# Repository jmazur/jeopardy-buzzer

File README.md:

# Jeopardy Buzzer
This project is a Jeopardy! inspired buzzer for home use. You can connect up to
10 contestants and 1 host to play trivia game. The first contestant to buzz in
locks all the other contestants out. 

The buzzers communicate over a local WIFI which can be configured in the
firmware.

## Hardware
This project uses an ESP 32 S2 SOLO. All schematics and PCB design was completed
using KiCAD. The full project can be found in the `pcb` folder.

There is a known issue with the spacing of the button contacts at the bottom of
the pcb, they need a little more space between them. They can still be used
as-is (which is why it didn't fixed earlier) but any new boards can use this
design change.

This project also uses a non-standard battery. I ran out of time to work on a
battery circuit to use a standard AA battery so I opted for a 
`3.2 Volt 600 mAh LiFePO4 14500 Battery` instead. It would be really nice to
change this to a single or a pair of AA or AAA batteries in a future version.

## Software
All firmware is compiled and sent to the ESP using the Arduino IDE. All files
are located in the `firmware` folder.

There is a flag called `IS_HOST` which differentiates buzzers between hosts and
contestants. There can only ever be 1 host per WIFI network. There can be up to
10 contestants before the network stops allowing new connections.

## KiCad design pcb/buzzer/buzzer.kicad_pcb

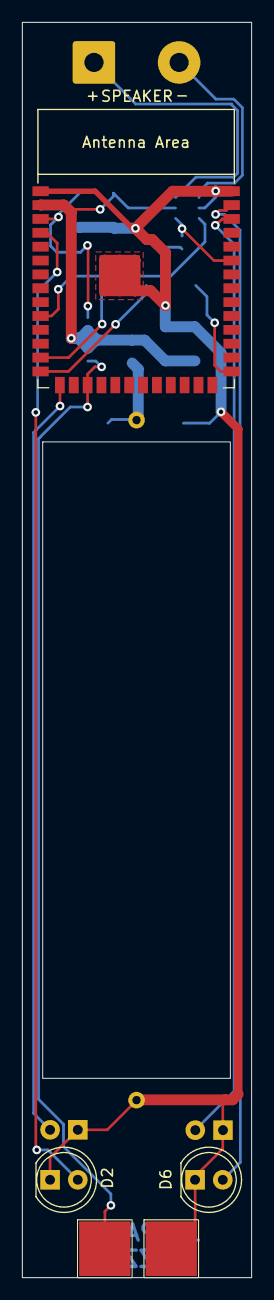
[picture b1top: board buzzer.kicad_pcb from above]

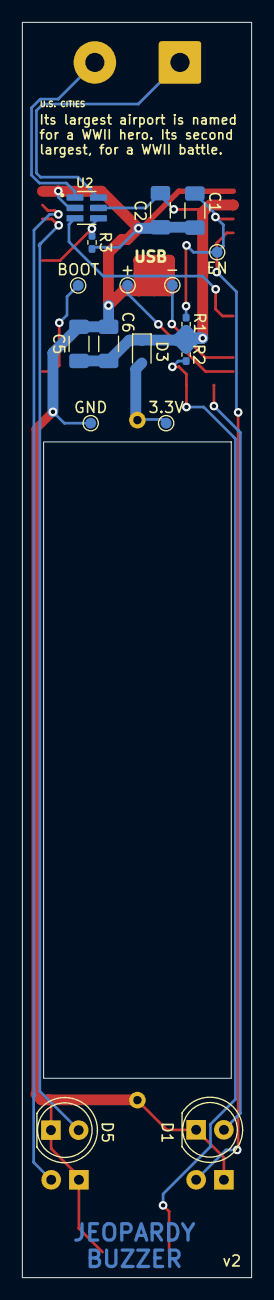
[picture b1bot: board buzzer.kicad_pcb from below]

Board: 2 copper layers, 21.0 x 115.0 mm, 24 parts (17 on the bottom side), 16 nets.

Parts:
3.3V: BATT; TestPoint_Pad_D1.0mm
+: USB_D +; TestPoint_Pad_D1.0mm
-: USB_D -; TestPoint_Pad_D1.0mm
BOOT: BOOT; TestPoint_Pad_D1.0mm
C1, C2, C5, C6: 22UF; C_1206_3216Metric_Pad1.33x1.80mm_HandSolder
Conn_Button_1, Conn_Button_2: Z00C-4G7L1-11000
D1, D2, D5, D6: LED; LED_D5.0mm_Clear
D3: BAT60A; D_SOD-323
EN: EN; TestPoint_Pad_D1.0mm
GND: GND; TestPoint_Pad_D1.0mm
J1: Conn_02x01; JM BATT 14500
R1: 10k; R_0402_1005Metric_Pad0.72x0.64mm_HandSolder
R2, R3: 10K; R_0402_1005Metric_Pad0.72x0.64mm_HandSolder
SPEAKER: Speaker; SolderWire-1sqmm_1x02_P7.8mm_D1.4mm_OD3.9mm
U1: ESP32-S2-SOLO
U2: PAM8301AAF; SOT95P280X145-6N

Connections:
3V3: C2.1, C5.1, C6.2, D3.1 (K), R1.1, R2.1, U1.2 (3V3), U2.5 (VDD)
AUDIO_SD: R3.1, U1.35 (MTMS/GPIO42), U2.4 (~SD)
BUTTON: Conn_Button_1.1, R2.2, U1.17 (GPIO9/TOUCH9/ADC1_CH8/FSPIHD)
GND: C1.2, C2.2, C5.2, C6.1, Conn_Button_2.1, D1.1 (K), D2.1 (K), D5.1 (K), D6.1 (K), GND.1, J1.2, R3.2, U1.1 (GND), U1.40 (GND), U1.41 (GND), U2.2 (GND)
LED1: D6.2 (A), U1.39 (GPIO1/TOUCH1/ADC1_CH0)
LED2: D5.2 (A), U1.38 (GPIO2/TOUCH2/ADC1_CH1)
LED3: D1.2 (A), U1.15 (GPIO3/TOUCH3/ADC1_CH2)
LED4: D2.2 (A), U1.4 (GPIO4/TOUCH4/ADC1_CH3)
unnamed: 3.3V.1, D3.2 (A), J1.1
unnamed: C1.1, EN.1, R1.2, U1.3 (EN)
unnamed: BOOT.1, U1.27 (GPIO0)
unnamed: U1.10 (GPIO17/U1TXD/ADC2_CH6/DAC_1), U2.3 (IN)
unnamed: -.1, U1.13 (GPIO19/U1RTS/ADC2_CH8/CLK_OUT2/USB_D-)
unnamed: +.1, U1.14 (GPIO20/U1CTS/ADC2_CH9/CLK_OUT1/USB_D+)
unnamed: SPEAKER.1, U2.6 (OUT+)
unnamed: SPEAKER.2, U2.1 (OUT-)

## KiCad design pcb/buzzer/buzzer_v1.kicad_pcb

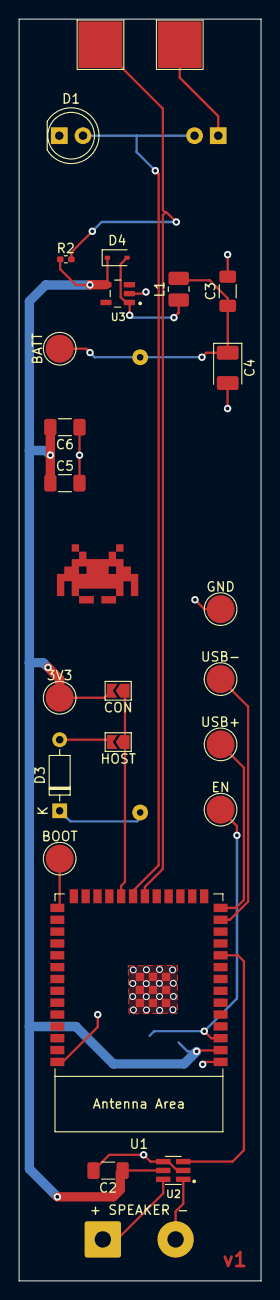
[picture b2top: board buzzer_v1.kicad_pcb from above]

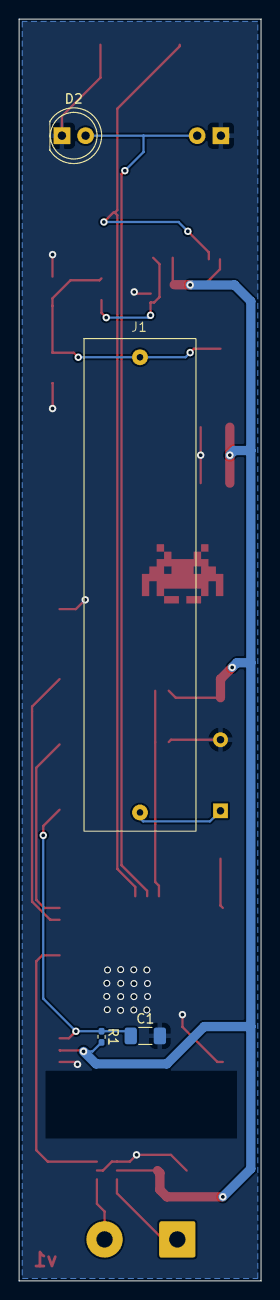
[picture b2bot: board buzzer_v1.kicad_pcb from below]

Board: 2 copper layers, 25.9 x 135.3 mm, 29 parts (4 on the bottom side), 15 nets.

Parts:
3V3: 3V3; TestPoint_Pad_D3.0mm
+ SPEAKER -: Speaker; SolderWire-1sqmm_1x02_P7.8mm_D1.4mm_OD3.9mm
BATT: BATT; TestPoint_Pad_D3.0mm
BOOT: BOOT; TestPoint_Pad_D3.0mm
C1, C2, C3, C5, C6: 22UF; C_1206_3216Metric_Pad1.33x1.80mm_HandSolder
C4: 150UF; CP_EIA-3528-12_Kemet-T_Pad1.50x2.35mm_HandSolder
CON: CONTESTANT; SolderJumper-2_P1.3mm_Open_TrianglePad1.0x1.5mm
Conn_Button_1, Conn_Button_2: Z00C-4G7L1-11000
D1, D2: LED; LED_D5.0mm_Clear
D3: D; D_DO-35_SOD27_P7.62mm_Horizontal
D4: BAT60A; D_SOD-323
EN: EN; TestPoint_Pad_D3.0mm
GND: GND; TestPoint_Pad_D3.0mm
HOST: HOST; SolderJumper-2_P1.3mm_Open_TrianglePad1.0x1.5mm
J1: Conn_02x01; Jm 1x AAA Battery Holder
L1: L; L_1008_2520Metric_Pad1.43x2.20mm_HandSolder
R1: 10k; R_0402_1005Metric_Pad0.72x0.64mm_HandSolder
R2: 10K; R_0402_1005Metric_Pad0.72x0.64mm_HandSolder
U1: ESP32-S2-SOLO
U2: PAM8301AAF; SOT95P280X145-6N
U3: TPS613221ADBVR; SOT95P280X145-5N
USB+: USB_D +; TestPoint_Pad_D3.0mm
USB-: USB_D -; TestPoint_Pad_D3.0mm

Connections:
3V3: 3V3.1, C2.1, C5.1, C6.2, CON.2 (B), D4.1 (K), R1.1, R2.1, U1.2 (3V3), U2.5 (VDD), U3.4 (VOUT)
GND: C1.2, C2.2, C3.2, C4.2, C5.2, C6.1, Conn_Button_2.1, D1.1 (K), D2.1 (K), D3.2 (A), GND.1, HOST.2 (B), U1.1 (GND), U1.40 (GND), U1.41 (GND), U2.2 (GND), U2.4 (~SD), U3.2 (GND)
unnamed: CON.1 (A), HOST.1 (A), U1.22 (GPIO14/TOUCH14/ADC2_CH3/FSPIWP/FSPIDQS)
unnamed: D1.2 (A), D2.2 (A), U1.21 (GPIO13/TOUCH13/ADC2_CH2/FSPIQ/FSPIIO7)
unnamed: D3.1 (K), J1.2
unnamed: D4.2 (A), L1.1, U3.1 (SW)
unnamed: BATT.1, C3.1, C4.1, J1.1, L1.2
unnamed: C1.1, EN.1, R1.2, U1.3 (EN)
unnamed: BOOT.1, U1.27 (GPIO0)
unnamed: Conn_Button_1.1, R2.2, U1.20 (GPIO12/TOUCH12/ADC2_CH1/FSPICLK/FSPIIO6)
unnamed: U1.10 (GPIO17/U1TXD/ADC2_CH6/DAC_1), U2.3 (IN)
unnamed: U1.13 (GPIO19/U1RTS/ADC2_CH8/CLK_OUT2/USB_D-), USB-.1
unnamed: U1.14 (GPIO20/U1CTS/ADC2_CH9/CLK_OUT1/USB_D+), USB+.1
unnamed: + SPEAKER -.1, U2.6 (OUT+)
unnamed: + SPEAKER -.2, U2.1 (OUT-)

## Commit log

2024-11-04 Add README
